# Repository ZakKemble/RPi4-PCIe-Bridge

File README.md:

Raspberry Pi 4 PCIe Bridge "Chip"
==================================

A drop-in replacement for the VL805 USB controller IC that bridges the PCIe bus signals to the USB 3.0 connector on the Raspberry Pi 4.

[https://blog.zakkemble.net/rpi4-pci-express-bridge-chip/](https://blog.zakkemble.net/rpi4-pci-express-bridge-chip/)

Instructions
------------

A hot air rework station is required for the removal of the VL805 chip and placement of the bridge chip.  There is a lot of copper inside the Raspberry Pi PCB so it may take a long time for it to heat up enough to melt the solder. The area around the chip should be covered with Kapton tape (or two layers of foil) to protect plastic parts and other sensitive components from excessive heat. Be careful not to knock off the tiny capacitors around the chip and don't forget to remove the microSD card! After removing the VL805 try to remove as much solder as possible from the PCB pads.

The bridge chip is larger than the original chip (8x10mm vs 8x8mm) and needs to be sanded down slightly so that the solder pads on the RPi PCB are visible and stick out from underneath the bridge when it is placed down. Use very fine sandpaper and be careful not to damage the traces at the edge of the board (other than making them shorter when sanding). Do not sand any further than the white line.

Apply a tiny amount of fresh solder paste onto the RPi PCB pads that are going to be soldered to the bridge chip (and maybe a bit of paste on the bridge chip too), then place down the bridge chip and reflow the solder. You might have to press the bridge chip down firmly while reflowing to make sure the pads make contact with each other and so that any excess solder from the large ground pad is pushed into the hole near the centre of the bridge chip.

Once the bridge chip has been installed it might also be a good idea to remove the SMD ferrite bead that normally passes through 1.03V for powering the VL805 USB controller (grey component marked #1 below). Removing it can help stop any accidental shorts from overloading the regulator, which also supplies power to the CPU core.

Without the VL805 chip the USB 5V power outputs will be disabled. To re-enable you will need to bridge two pins with a bit of solder (6 pin IC marked #2 below, the two pins nearest the screw hole). Be careful, as some PCIe risers are not supposed to have 5V connected.

Now wait for everything to cool down and let's hope it works!

| PCIe Signal | USB Signal       | Direction                |
| ----------- | ---------------- | ------------------------ |
| REFCLK+     | D-               | Host -> Device           |
| REFCLK-     | D+               | Host -> Device           |
| HSO+        | RX-              | Host (TX) -> Device (RX) |
| HSO-        | RX+              | Host (TX) -> Device (RX) |
| HSI+        | TX-              | Device (TX) -> Host (RX) |
| HSI-        | TX+              | Device (TX) -> Host (RX) |
| RESET       | D- (lower port)  | Host -> Device           |
| WAKE (not connected on the Pi) | D+ (lower port)  | Device -> Host           |
| CLKREQ      | RX+ (lower port) | Host -> Device           |
| PONRST      | RX- (lower port) | Not a PCIe signal, connected like a reset pin on a microcontroller. |

NOTE: The PCIe spec allows for polarity inversion, where the + and - signals are allowed to be swapped.

--------

Zak Kemble

contact@zakkemble.net

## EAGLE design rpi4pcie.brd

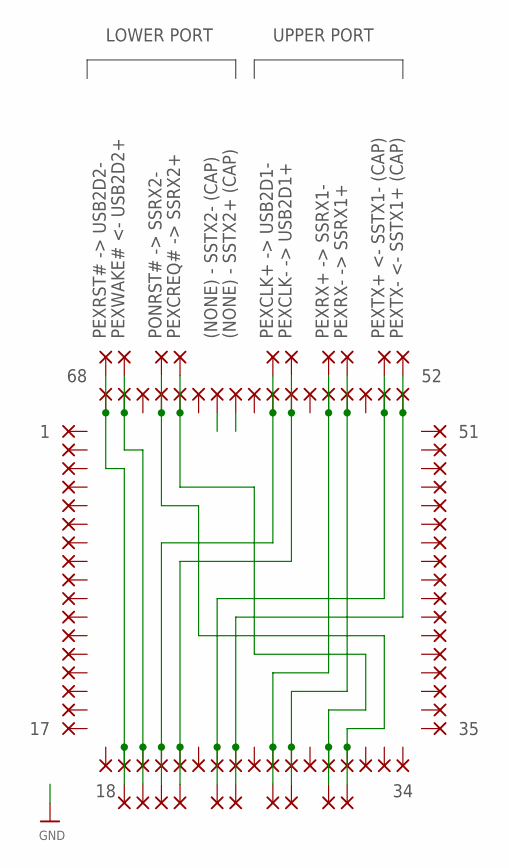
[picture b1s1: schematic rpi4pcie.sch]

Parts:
PAD1, PAD2, PAD3, PAD4, PAD5, PAD6, PAD7, PAD8, PAD9, PAD10, PAD11, PAD12, PAD13, PAD14, PAD15, PAD16, PAD17, PAD18, PAD19, PAD20, PAD21, PAD22, PAD23, PAD24, PAD25, PAD26, PAD27, PAD28, PAD29, PAD30, PAD31, PAD32, PAD33, PAD34, PAD35, PAD36, PAD37, PAD38, PAD39, PAD40, PAD41, PAD42, PAD43, PAD44, PAD45, PAD46, PAD47, PAD48, PAD49, PAD50, PAD51, PAD52, PAD53, PAD54, PAD55, PAD56, PAD57, PAD58, PAD59, PAD60, PAD61, PAD62, PAD63, PAD64, PAD65, PAD66, PAD67, PAD68, PAD69, PAD70, PAD71, PAD72, PAD73, PAD74, PAD75, PAD76, PAD77, PAD78, PAD79, PAD80, PAD81, PAD82, PAD83, PAD84, PAD85, PAD86, PAD87, PAD88: PADQFN-0.4; PAD-QFN-0.4

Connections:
unnamed: PAD19.1, PAD68.1, PAD69.1, PAD77.1
unnamed: PAD20.1, PAD67.1, PAD70.1, PAD78.1
unnamed: PAD21.1, PAD59.1, PAD71.1, PAD79.1
unnamed: PAD22.1, PAD58.1, PAD72.1, PAD80.1
unnamed: PAD25.1, PAD52.1, PAD76.1, PAD82.1
unnamed: PAD31.1, PAD65.1, PAD86.1, PAD87.1
unnamed: PAD27.1, PAD56.1, PAD73.1, PAD83.1
unnamed: PAD28.1, PAD55.1, PAD74.1, PAD84.1
unnamed: PAD24.1, PAD53.1, PAD75.1, PAD81.1
unnamed: PAD30.1, PAD64.1, PAD85.1, PAD88.1

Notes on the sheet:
PEXRST# -> USB2D2-
PEXWAKE# <- USB2D2+
PONRST# -> SSRX2-
PEXCREQ# -> SSRX2+
PEXCLK+ -> USB2D1-
PEXCLK- -> USB2D1+
PEXRX+ -> SSRX1-
PEXRX- -> SSRX1+
PEXTX+ <- SSTX1- (CAP)
PEXTX- <- SSTX1+ (CAP)
(NONE) - SSTX2- (CAP)
(NONE) - SSTX2+ (CAP)
LOWER PORT
UPPER PORT

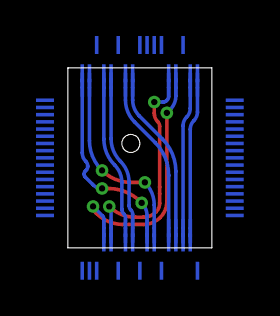
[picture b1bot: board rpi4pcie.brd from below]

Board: 2 copper layers, 8.0 x 10.0 mm, 88 parts (88 on the bottom side), 10 nets.

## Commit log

2020-06-14 Initial commit :banana:
2020-11-26 Add instructions

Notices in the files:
parts and their libraries:
microbuilder: This work is placed in the public domain, and may be freely used for commercial and non-commercial work with the following conditions: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
